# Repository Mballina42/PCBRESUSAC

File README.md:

# PCBRESUSAC
Proyecto en kicad
Parte del Hardware
3 Nema 17
3 Limmit Switch opticos
1 Esp32
entre otros.

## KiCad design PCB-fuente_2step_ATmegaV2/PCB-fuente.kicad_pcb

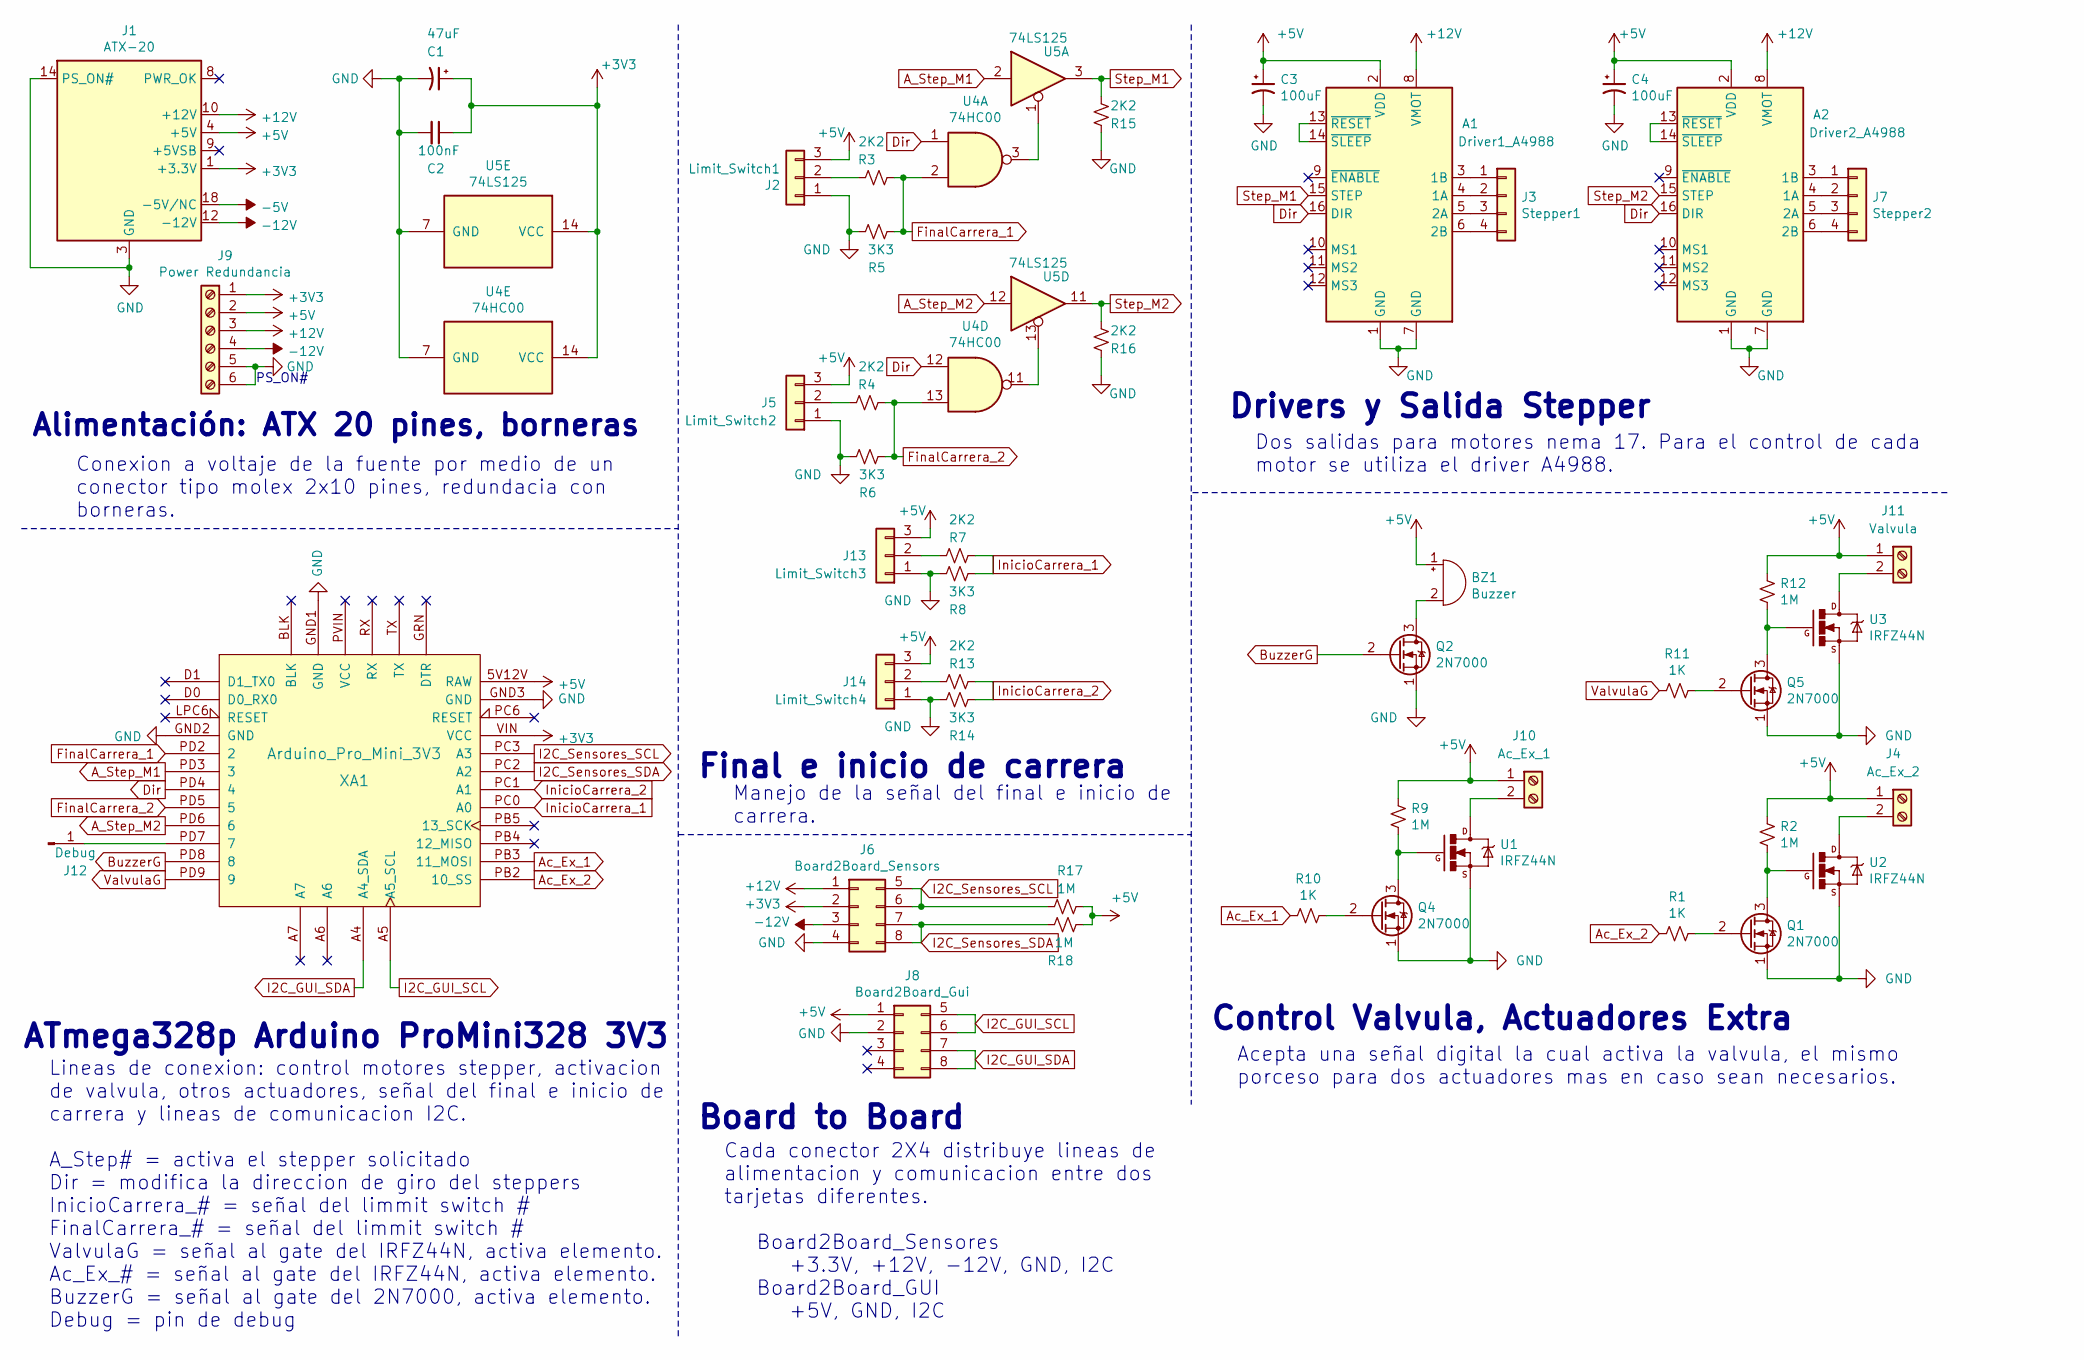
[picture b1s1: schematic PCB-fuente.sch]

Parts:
A1: Driver1_A4988; Pololu_Breakout-16_15.2x20.3mm
A2: Driver2_A4988; Pololu_Breakout-16_15.2x20.3mm
BZ1: Buzzer; Buzzer_12x9.5RM7.6
C1: 47uF; CP_Radial_D5.0mm_P2.50mm
C2: 100nF; C_0805_2012Metric
C3, C4: 100uF; CP_Radial_D5.0mm_P2.50mm
J1: ATX-20; Molex_Mini-Fit_Jr_5566-20A_2x10_P4.20mm_Vertical
J2: Limit_Switch1; Molex_KK-254_AE-6410-03A_1x03_P2.54mm_Vertical
J3: Stepper1; Molex_KK-254_AE-6410-04A_1x04_P2.54mm_Vertical
J4: Ac_Ex_2; TerminalBlock_bornier-2_P5.08mm
J5: Limit_Switch2; Molex_KK-254_AE-6410-03A_1x03_P2.54mm_Vertical
J6: Board2Board_Sensors; PinSocket_2x04_P2.54mm_Vertical
J7: Stepper2; Molex_KK-254_AE-6410-04A_1x04_P2.54mm_Vertical
J8: Board2Board_Gui; PinSocket_2x04_P2.54mm_Vertical
J9: Power Redundancia; TerminalBlock_bornier-6_P5.08mm
J10: Ac_Ex_1; TerminalBlock_bornier-2_P5.08mm
J11: Valvula; TerminalBlock_bornier-2_P5.08mm
J12: Debug; Pin_D1.3mm_L11.0mm
J13: Limit_Switch3; Molex_KK-254_AE-6410-03A_1x03_P2.54mm_Vertical
J14: Limit_Switch4; Molex_KK-254_AE-6410-03A_1x03_P2.54mm_Vertical
Q1, Q2, Q4, Q5: 2N7000; TO-92_Inline
R1, R10, R11: 1K; R_0805_2012Metric
R2, R9, R12, R17, R18: 1M; R_0805_2012Metric
R3, R4, R7, R13, R15, R16: 2K2; R_0805_2012Metric
R5, R6, R8, R14: 3K3; R_0805_2012Metric
U1, U2, U3: IRFZ44N; TO-220F-3_Vertical
U4: 74HC00
U5: 74LS125
XA1: Arduino_Pro_Mini_3V3; Arduino_Mini_Socket

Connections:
+3V3: C1.1, C2.1, J1.1 (+3.3V), J1.2 (+3.3V), J1.11 (+3.3V), J6.2, J9.1, U4.14 (VCC), U5.14 (VCC), XA1.VIN (VCC)
+5V: A1.2 (VDD), A2.2 (VDD), BZ1.1 (-), C3.1, C4.1, J1.4 (+5V), J1.6 (+5V), J1.19 (+5V), J1.20 (+5V), J2.3, J4.1, J5.3, J8.1, J9.2, J10.1, J11.1, J13.3, J14.3, R2.1, R9.1, R12.1, R17.1, R18.2, XA1.5V12V (RAW)
+12V: A1.8 (VMOT), A2.8 (VMOT), J1.10 (+12V), J6.1, J9.3
-5V: J1.18 (-5V/NC)
-12V: J1.12 (-12V), J6.3, J9.4
A_Step_M1: U5.2, XA1.PD3 (3)
A_Step_M2: U5.12, XA1.PD6 (6)
Ac_Ex_1: R10.2, XA1.PB3 (11_MOSI)
Ac_Ex_2: R1.2, XA1.PB2 (10_SS)
BuzzerG: Q2.2 (G), XA1.PD8 (8)
Dir: A1.16 (DIR), A2.16 (DIR), U4.1, U4.12, XA1.PD4 (4)
FinalCarrera_1: R3.1, R5.2, U4.2, XA1.PD2 (2)
FinalCarrera_2: R4.1, R6.2, U4.13, XA1.PD5 (5)
GND: A1.1 (GND), A1.7 (GND), A2.1 (GND), A2.7 (GND), C1.2, C2.2, C3.2, C4.2, J1.3 (GND), J1.5 (GND), J1.7 (GND), J1.13 (GND), J1.14 (PS_ON#), J1.15 (GND), J1.16 (GND), J1.17 (GND), J2.1, J5.1, J6.4, J8.2, J9.5, J9.6, J13.1, J14.1, Q1.1 (S), Q2.1 (S), Q4.1 (S), Q5.1 (S), R5.1, R6.1, R8.1, R14.1, R15.2, R16.2, U1.3 (S), U2.3 (S), U3.3 (S), U4.7 (GND), U5.7 (GND), XA1.GND1 (GND), XA1.GND2 (GND), XA1.GND3 (GND)
I2C_GUI_SCL: J8.5, J8.6, XA1.A5 (A5_SCL)
I2C_GUI_SDA: J8.7, J8.8, XA1.A4 (A4_SDA)
I2C_Sensores_SCL: J6.5, J6.6, R17.2, XA1.PC3 (A3)
I2C_Sensores_SDA: J6.7, J6.8, R18.1, XA1.PC2 (A2)
InicioCarrera_1: R7.2, R8.2, XA1.PC0 (A0)
InicioCarrera_2: R13.2, R14.2, XA1.PC1 (A1)
unnamed: A1.3 (1B), J3.1
unnamed: A1.4 (1A), J3.2
unnamed: A1.5 (2A), J3.3
unnamed: A1.6 (2B), J3.4
unnamed: A1.13 (~RESET), A1.14 (~SLEEP)
unnamed: A2.3 (1B), J7.1
unnamed: A2.4 (1A), J7.2
unnamed: A2.5 (2A), J7.3
unnamed: A2.6 (2B), J7.4
unnamed: A2.13 (~RESET), A2.14 (~SLEEP)
unnamed: BZ1.2 (+), Q2.3 (D)
unnamed: J2.2, R3.2
unnamed: J4.2, U2.2 (D)
unnamed: J5.2, R4.2
unnamed: J10.2, U1.2 (D)
unnamed: J11.2, U3.2 (D)
unnamed: J12.1, XA1.PD7 (7)
unnamed: J13.2, R7.1
unnamed: J14.2, R13.1
unnamed: Q1.2 (G), R1.1
unnamed: Q1.3 (D), R2.2, U2.1 (G)
unnamed: Q4.2 (G), R10.1
unnamed: Q4.3 (D), R9.2, U1.1 (G)
unnamed: Q5.2 (G), R11.1
unnamed: Q5.3 (D), R12.2, U3.1 (G)
unnamed: U4.3, U5.1
unnamed: U4.11, U5.13
Step_M1: A1.15 (STEP), R15.1, U5.3
Step_M2: A2.15 (STEP), R16.1, U5.11
ValvulaG: R11.2, XA1.PD9 (9)

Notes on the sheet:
Alimentación: ATX 20 pines, borneras
Drivers y Salida Stepper
ATmega328p Arduino ProMini328 3V3
Conexion a voltaje de la fuente por medio de un conector tipo molex 2x10 pines, redundacia con borneras.
Dos salidas para motores nema 17. Para el control de cada motor se utiliza el driver A4988.
Lineas de conexion: control motores stepper, activacion de valvula, otros actuadores, señal del final e inicio de carrera y lineas de comunicacion I2C. A_Step# = activa el stepper solicitado Dir = modifica la direccion de giro del steppers InicioCarrera_# = señal del limmit switch # FinalCarrera_# 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
Board to Board
Cada conector 2X4 distribuye lineas de alimentacion y comunicacion entre dos tarjetas diferentes. Board2Board_Sensores +3.3V, +12V, -12V, GND, I2C Board2Board_GUI +5V, GND, I2C
Final e inicio de carrera
Manejo de la señal del final e inicio de carrera.
Acepta una señal digital la cual activa la valvula, el mismo porceso para dos actuadores mas en caso sean necesarios.
Control Valvula, Actuadores Extra
PS_ON#

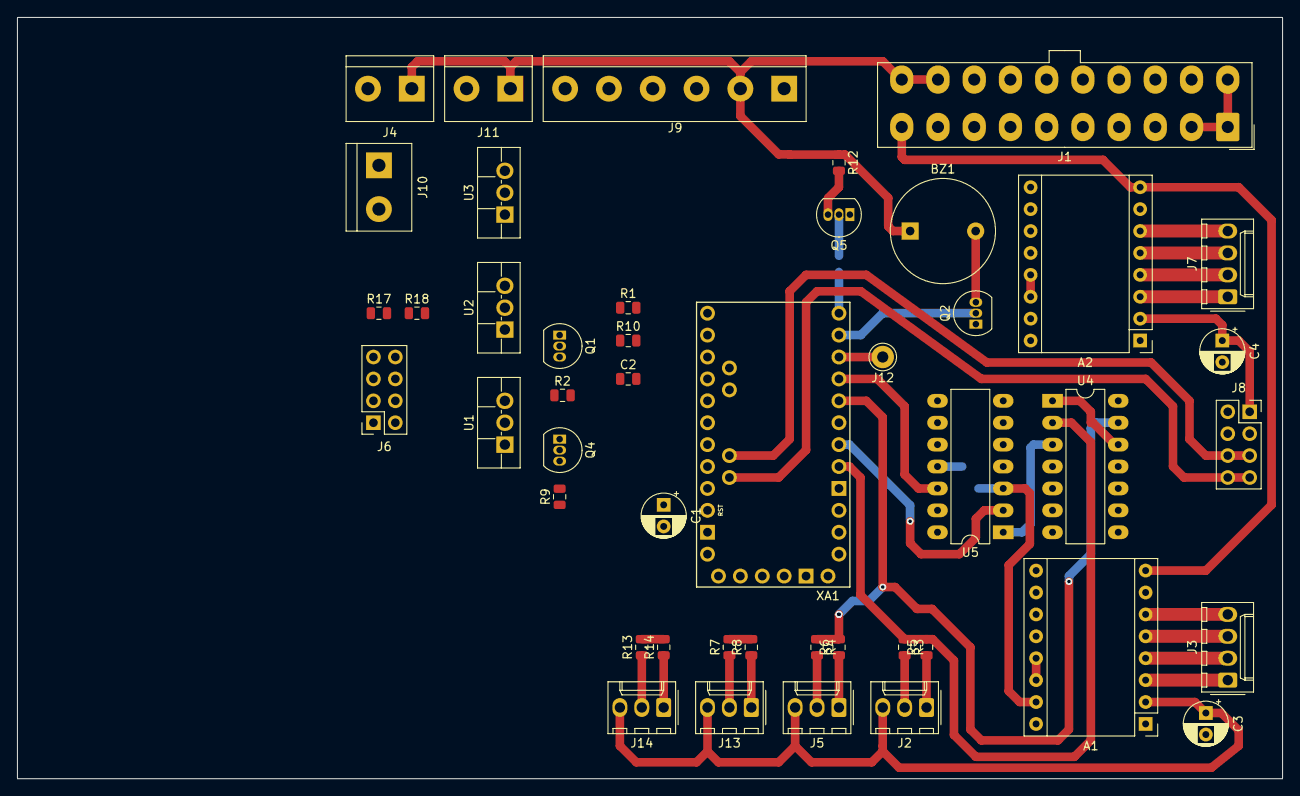
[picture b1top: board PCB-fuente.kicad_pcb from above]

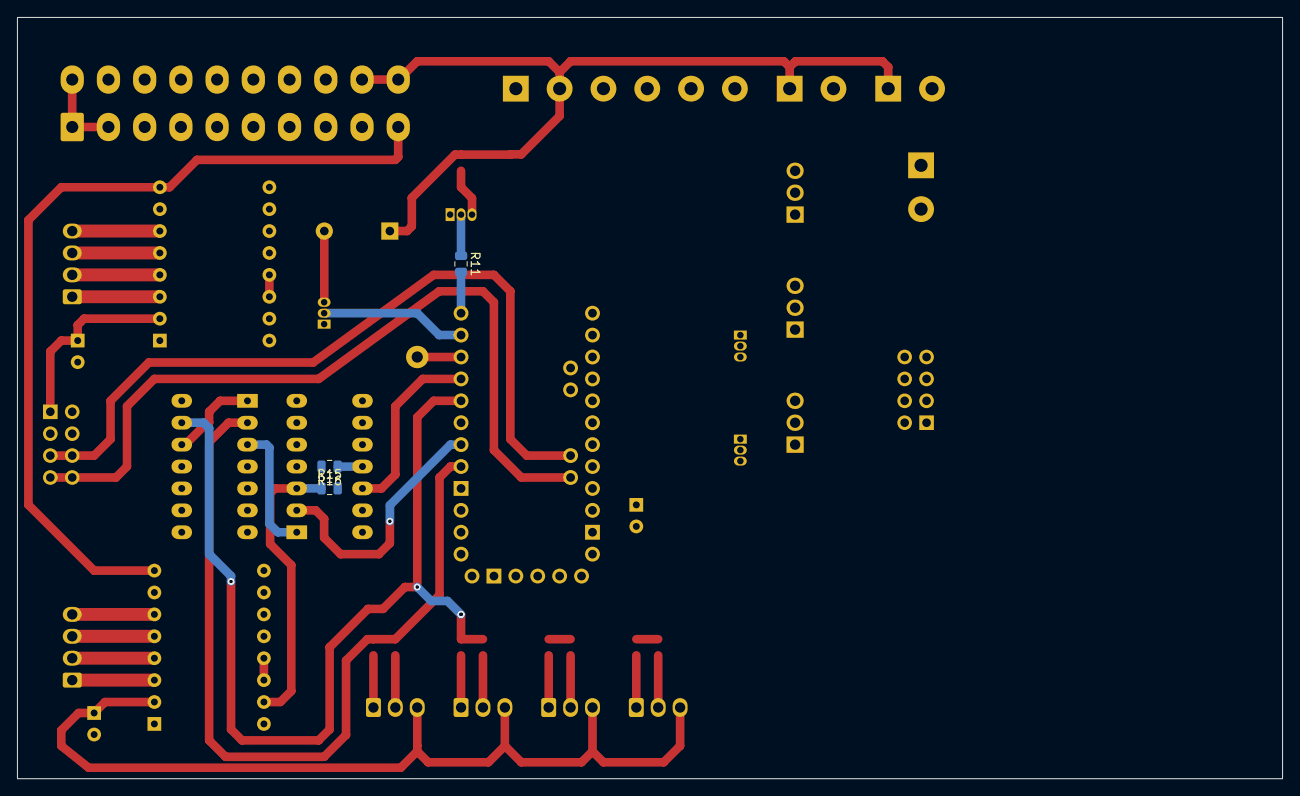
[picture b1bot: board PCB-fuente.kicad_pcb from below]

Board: 2 copper layers, 146.7 x 88.3 mm, 49 parts (3 on the bottom side), 49 nets.

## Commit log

2020-04-24 UPDATE 24-04-20
2020-04-24 UPDATE 24-04-20 p2
2020-05-03 update 3-5-20
2020-06-03 update 2-6-20
2020-06-03 NEW UPDATE 2-6-20
2020-06-11 UPDATE 11-6-20
